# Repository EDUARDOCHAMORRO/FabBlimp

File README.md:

# [Fab Blimp] Workshop

 Workshop developped for Fab15 Egypt Conference by Eduardo Chamorro and Santi Fuentemilla

 Workshop of producing and fabricating a phone controlled blimp. Pcb fabricated with a Roland SRM20, blimp balloon produced by sealing a plastics bags with a CO2 lasercutter and frame made out of cardboard cutted also with the lasercutter.
 Control of the blimp via an smartphone accessing the ip address of the ESP12 via an internal wifi access point(wifi connection required)

[PDF DOWNLOAD GUIDE ON HOW TO ASSEMBLE IT](https://eduardochamorro.github.io/FabBlimp/fabblimp.pdf)

## Hardware Requirements

- Pcb Fr1
- 3x brushed motors 0615 size
- 3x propellers tinywhoop
- Ftdi cable 3.3v
- Corrugated Card 360 kg/m3
- Glue gun
-	Double side tape
- Cutters
-	Scissors
- Helium Kit ,Tank 14.9 cu.ft
- 36 Inch Giant Latex Balloon White
- Electronics		RES 100 OHM 1/4W 1% 1206 SMD
- Electronics		RES 10.0K OHM 1/4W 1% 1206 SMD
- Electronics		CAP CER 4.7UF 35V Y5V 1206
- Electronics		CAP CER 10UF 35V Y5V 1206
- Electronics		MOSFET N-CH 30V 1.7A SSOT3
- Electronics		SMT RT Angle Male Header 0.1" (36pos)
- Electronics		SWITCH TACT SMD W-GND 160GF
- Electronics		Esp8266 Esp-12e
- Electronics		IC REG LDO 3.3V 1A SOT223-3

## PCB production files

**FILES WITH MOTOR HOLDER**

**FILES WITHOUT MOTOR HOLDER**

## Cut out file for a lasercutter motor holder

[Download Laser Cut file dxf](https://eduardochamorro.github.io/FabBlimp/dock.dxf)

## Control app via browser

There is two version of the code.

1- WIFI SERVER : the blimp connects to an already existing wifi hotspot and uses that network to increase the control range and improved webpage control.(longer range and more visual)

2- WIFI HOTSPOT : for not stable or fast enough wifi hotspots, the blimp creates his own hotspot and get controlled by publishing an control webpage.(faster control,shorter range and less visual)

## Copyright and License

Copyright3-2019 FabLab BCN - IaaC. Code released under the [MIT](https://github.com/BlackrockDigital/startbootstrap-freelancer/blob/gh-pages/LICENSE) license.
Developped by Eduardo Chamorro and Santi Fuentemilla. July 2019
Updated by Miriam Choi February 2020

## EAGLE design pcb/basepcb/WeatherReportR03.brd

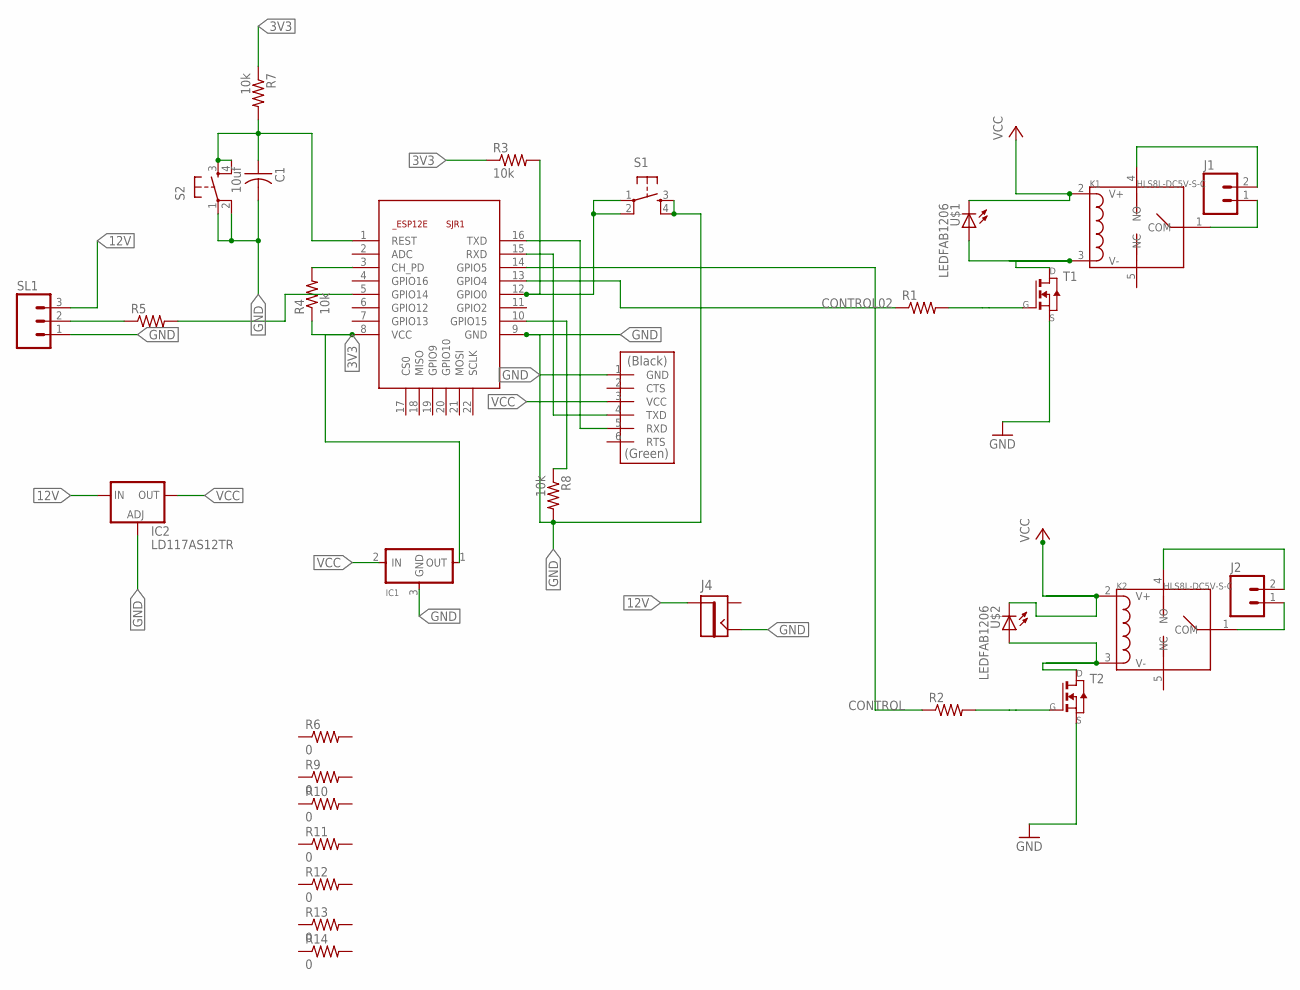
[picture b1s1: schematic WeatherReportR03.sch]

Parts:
C1: 10uf; C1206FAB
IC1: REGULATORSOT23; SOT23
IC2: LD117AS12TR; SOT223
J1, J2: M02POLAR_LOCK; MOLEX-1X2_LOCK
J4: JACK2.1MM; JACK_2.1MM
K1, K2: HLS8L-DC5V-S-C; REY5-19.0X15.0X15.0MM
R1, R2, R5: RES-US1206FAB; R1206FAB
R3, R4, R7, R8: 10k; R1206FAB
R6, R9, R10, R11, R12, R13, R14: 0; R1206FAB
S1, S2: 6MM_SWITCH6MM_SWITCH; 6MM_SWITCH
SJR1: ESP8266-12EESP12E; ESP8266-ESP12E
SL1: M03; 03P
T1, T2: NMOSFETSOT23; SOT-23
U$1, U$2: LEDFAB1206; LED1206FAB
U$7: FTDI-SMD-HEADER; 1X06SMD

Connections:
3V3: IC1.1 (OUT), R3.1, R4.1, R7.1, SJR1.8 (VCC)
12V: IC2.3 (IN), J4.PIN, SL1.3
CONTROL: R2.1, SJR1.14 (GPIO5)
CONTROL02: R1.1, SJR1.13 (GPIO4)
GND: C1.2, IC1.3 (GND), IC2.1 (ADJ), J4.CONTACT, R8.2, S1.3 (S), S1.4 (S1), S2.1, S2.2 (P1), SJR1.9 (GND), SL1.1, T1.2 (S), T2.2 (S), U$7.1 (GND)
unnamed: R1.2, T1.3 (G)
unnamed: K1.3 (V-), T1.1 (D), U$1.1 (A)
unnamed: SJR1.16 (TXD), U$7.5 (RXD)
unnamed: SJR1.15 (RXD), U$7.4 (TXD)
unnamed: R8.1, SJR1.10 (GPIO15)
unnamed: J1.2, K1.4 (NO)
unnamed: J1.1, K1.1 (COM)
unnamed: R3.2, S1.1, S1.2 (P1), SJR1.12 (GPIO0)
unnamed: R5.2, SJR1.5 (GPIO14)
unnamed: K2.3 (V-), T2.1 (D), U$2.1 (A)
unnamed: C1.1, R7.2, S2.3 (S), S2.4 (S1), SJR1.1 (REST)
unnamed: R2.2, T2.3 (G)
unnamed: J2.2, K2.4 (NO)
unnamed: J2.1, K2.1 (COM)
unnamed: R4.2, SJR1.3 (CH_PD)
unnamed: R5.1, SL1.2
VCC: IC1.2 (IN), IC2.4 (OUT), K1.2 (V+), K2.2 (V+), U$1.2 (C), U$2.2 (C), U$7.3 (VCC)

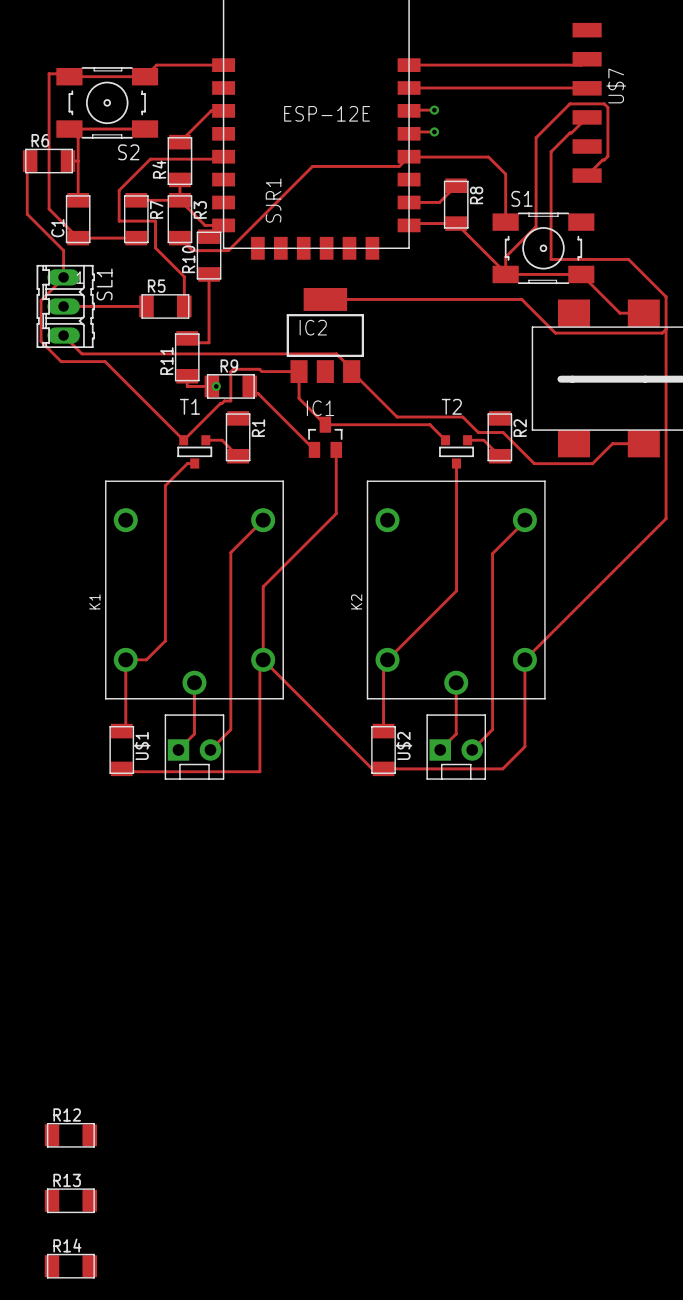
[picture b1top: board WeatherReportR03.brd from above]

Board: 2 copper layers, 31 parts (0 on the bottom side), 22 nets.

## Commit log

2019-07-08 first test
2019-07-08 fix pages
2019-07-24 public push
2019-08-01 workshop push
2019-10-15 update workshop
2019-10-29 Bump lodash.template from 4.4.0 to 4.5.0 in /webpage
    Bumps [lodash.template](https://github.com/lodash/lodash) from 4.4.0 to 4.5.0.
    - [Release notes](https://github.com/lodash/lodash/releases)
    - [Commits](https://github.com/lodash/lodash/compare/4.4.0...4.5.0)
2020-03-04 update by miriam
2020-03-04 clean repo
2020-03-04 Bump lodash from 4.17.11 to 4.17.15 in /webpage
    Bumps [lodash](https://github.com/lodash/lodash) from 4.17.11 to 4.17.15.
    - [Release notes](https://github.com/lodash/lodash/releases)
    - [Commits](https://github.com/lodash/lodash/compare/4.17.11...4.17.15)
2020-03-04 Bump mixin-deep from 1.3.1 to 1.3.2 in /webpage
    Bumps [mixin-deep](https://github.com/jonschlinkert/mixin-deep) from 1.3.1 to 1.3.2.
    - [Release notes](https://github.com/jonschlinkert/mixin-deep/releases)
    - [Commits](https://github.com/jonschlinkert/mixin-deep/compare/1.3.1...1.3.2)
2020-03-19 pdf change
2020-04-30 Bump jquery from 3.4.1 to 3.5.0 in /webpage
    Bumps [jquery](https://github.com/jquery/jquery) from 3.4.1 to 3.5.0.
    - [Release notes](https://github.com/jquery/jquery/releases)
    - [Commits](https://github.com/jquery/jquery/compare/3.4.1...3.5.0)
2020-07-17 Bump lodash from 4.17.11 to 4.17.19 in /webpage
    Bumps [lodash](https://github.com/lodash/lodash) from 4.17.11 to 4.17.19.
    - [Release notes](https://github.com/lodash/lodash/releases)
    - [Commits](https://github.com/lodash/lodash/compare/4.17.11...4.17.19)
2020-09-04 Bump node-sass from 4.12.0 to 4.14.1 in /webpage
    Bumps [node-sass](https://github.com/sass/node-sass) from 4.12.0 to 4.14.1.
    - [Release notes](https://github.com/sass/node-sass/releases)
    - [Changelog](https://github.com/sass/node-sass/blob/master/CHANGELOG.md)
    - [Commits](https://github.com/sass/node-sass/compare/v4.12.0...v4.14.1)
2020-12-11 Bump ini from 1.3.5 to 1.3.7 in /webpage
    Bumps [ini](https://github.com/isaacs/ini) from 1.3.5 to 1.3.7.
    - [Release notes](https://github.com/isaacs/ini/releases)
    - [Commits](https://github.com/isaacs/ini/compare/v1.3.5...v1.3.7)
2021-03-31 Bump y18n from 3.2.1 to 3.2.2 in /webpage
    Bumps [y18n](https://github.com/yargs/y18n) from 3.2.1 to 3.2.2.
    - [Release notes](https://github.com/yargs/y18n/releases)
    - [Changelog](https://github.com/yargs/y18n/blob/master/CHANGELOG.md)
    - [Commits](https://github.com/yargs/y18n/commits)
2021-04-06 repo fix
2021-05-10 Bump lodash from 4.17.11 to 4.17.21 in /webpage
    Bumps [lodash](https://github.com/lodash/lodash) from 4.17.11 to 4.17.21.
    - [Release notes](https://github.com/lodash/lodash/releases)
    - [Commits](https://github.com/lodash/lodash/compare/4.17.11...4.17.21)
2021-05-10 Bump hosted-git-info from 2.7.1 to 2.8.9 in /webpage
    Bumps [hosted-git-info](https://github.com/npm/hosted-git-info) from 2.7.1 to 2.8.9.
    - [Release notes](https://github.com/npm/hosted-git-info/releases)
    - [Changelog](https://github.com/npm/hosted-git-info/blob/v2.8.9/CHANGELOG.md)
    - [Commits](https://github.com/npm/hosted-git-info/compare/v2.7.1...v2.8.9)
2021-05-25 Bump browserslist from 4.6.1 to 4.16.6 in /webpage
    Bumps [browserslist](https://github.com/browserslist/browserslist) from 4.6.1 to 4.16.6.
    - [Release notes](https://github.com/browserslist/browserslist/releases)
    - [Changelog](https://github.com/browserslist/browserslist/blob/main/CHANGELOG.md)
    - [Commits](https://github.com/browserslist/browserslist/compare/4.6.1...4.16.6)
2021-06-16 Bump postcss from 7.0.16 to 7.0.36 in /webpage
    Bumps [postcss](https://github.com/postcss/postcss) from 7.0.16 to 7.0.36.
    - [Release notes](https://github.com/postcss/postcss/releases)
    - [Changelog](https://github.com/postcss/postcss/blob/main/CHANGELOG.md)
    - [Commits](https://github.com/postcss/postcss/compare/7.0.16...7.0.36)
    ---
    updated-dependencies:
2021-08-11 Bump path-parse from 1.0.6 to 1.0.7 in /webpage
    Bumps [path-parse](https://github.com/jbgutierrez/path-parse) from 1.0.6 to 1.0.7.
    - [Release notes](https://github.com/jbgutierrez/path-parse/releases)
    - [Commits](https://github.com/jbgutierrez/path-parse/commits/v1.0.7)
    ---
    updated-dependencies:
    - dependency-name: path-parse
2022-02-12 Bump ajv from 6.10.0 to 6.12.6 in /webpage
    Bumps [ajv](https://github.com/ajv-validator/ajv) from 6.10.0 to 6.12.6.
    - [Release notes](https://github.com/ajv-validator/ajv/releases)
    - [Commits](https://github.com/ajv-validator/ajv/compare/v6.10.0...v6.12.6)
    ---
    updated-dependencies:
    - dependency-name: ajv
2022-06-27 Bump copy-props from 2.0.4 to 2.0.5 in /webpage
    Bumps [copy-props](https://github.com/gulpjs/copy-props) from 2.0.4 to 2.0.5.
    - [Release notes](https://github.com/gulpjs/copy-props/releases)
    - [Changelog](https://github.com/gulpjs/copy-props/blob/master/CHANGELOG.md)
    - [Commits](https://github.com/gulpjs/copy-props/compare/2.0.4...2.0.5)
    ---
    updated-dependencies:
2022-10-30 Bump socket.io-parser and browser-sync in /webpage
    Bumps [socket.io-parser](https://github.com/socketio/socket.io-parser) to 4.2.1 and updates ancestor dependency [browser-sync](https://github.com/BrowserSync/browser-sync). These dependencies need to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
    Updates `socket.io-parser` from 3.2.0 to 4.2.1
    - [Release notes](https://github.com/socketio/socket.io-parser/releases)
    - [Changelog](https://github.com/socketio/socket.io-parser/blob/main/CHANGELOG.md)
    - [Commits](https://github.com/socketio/socket.io-parser/compare/3.2.0...4.2.1)
    Updates `browser-sync` from 2.26.7 to 2.27.10
2022-11-23 Bump engine.io and browser-sync in /webpage
    Bumps [engine.io](https://github.com/socketio/engine.io) to 6.2.1 and updates ancestor dependency [browser-sync](https://github.com/BrowserSync/browser-sync). These dependencies need to be updated to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
    Updates `engine.io` from 3.2.1 to 6.2.1
    - [Release notes](https://github.com/socketio/engine.io/releases)
    - [Changelog](https://github.com/socketio/engine.io/blob/main/CHANGELOG.md)
    - [Commits](https://github.com/socketio/engine.io/compare/3.2.1...6.2.1)
    Updates `browser-sync` from 2.26.7 to 2.27.10
2022-12-04 Bump decode-uri-component from 0.2.0 to 0.2.2 in /webpage
    Bumps [decode-uri-component](https://github.com/SamVerschueren/decode-uri-component) from 0.2.0 to 0.2.2.
    - [Release notes](https://github.com/SamVerschueren/decode-uri-component/releases)
    - [Commits](https://github.com/SamVerschueren/decode-uri-component/compare/v0.2.0...v0.2.2)
    ---
    updated-dependencies:
    - dependency-name: decode-uri-component

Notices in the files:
parts and their libraries:
SparkFun-Connectors: Licensing: Creative Commons ShareAlike 4.0 International - https://creativecommons.org/licenses/by-sa/4.0
